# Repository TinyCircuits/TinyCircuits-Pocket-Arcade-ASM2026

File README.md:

# TinyCircuits Pocket Arcade
# ASM2026 Rev3

The design files are located under design_files/ for the TinyCircuits ASM2026 Rev 3 PCB. This is a tiny arcade game machine powered by Arduino software.

Format is in Cadsoft Eagle format - Eagle version 6.2 was used for the original design.

For more infomation on this, check out the product page at TinyCircuits.com: https://tinycircuits.com/collections/all/products/pocket-arcade

# License:

Design by TinyCircuits.
All design files are released under the Creative Commons Attribution Share-Alike 3.0 License, see the following link for details: http://creativecommons.org/licenses/by-sa/3.0

All text above must be included in any redistribution or derived design

This project uses designs and concepts developed as part of the Arduino project and the LilyPad project.  The TinyCircuits design files themselves (schematics, PCB and libraries) are not directly derived from these works' design files and have been created new, however the concepts and basic architecture behind the TinyDuino and TinyLily products are derived and we thank the hard work of the organizations below for their contributions to open-source hardware:
  
Original Arduino Uno Design by Team Arduino

LilyPad Arduino Design by Leah Buechley and Sparkfun Electronics

Please support the open-source hardware community

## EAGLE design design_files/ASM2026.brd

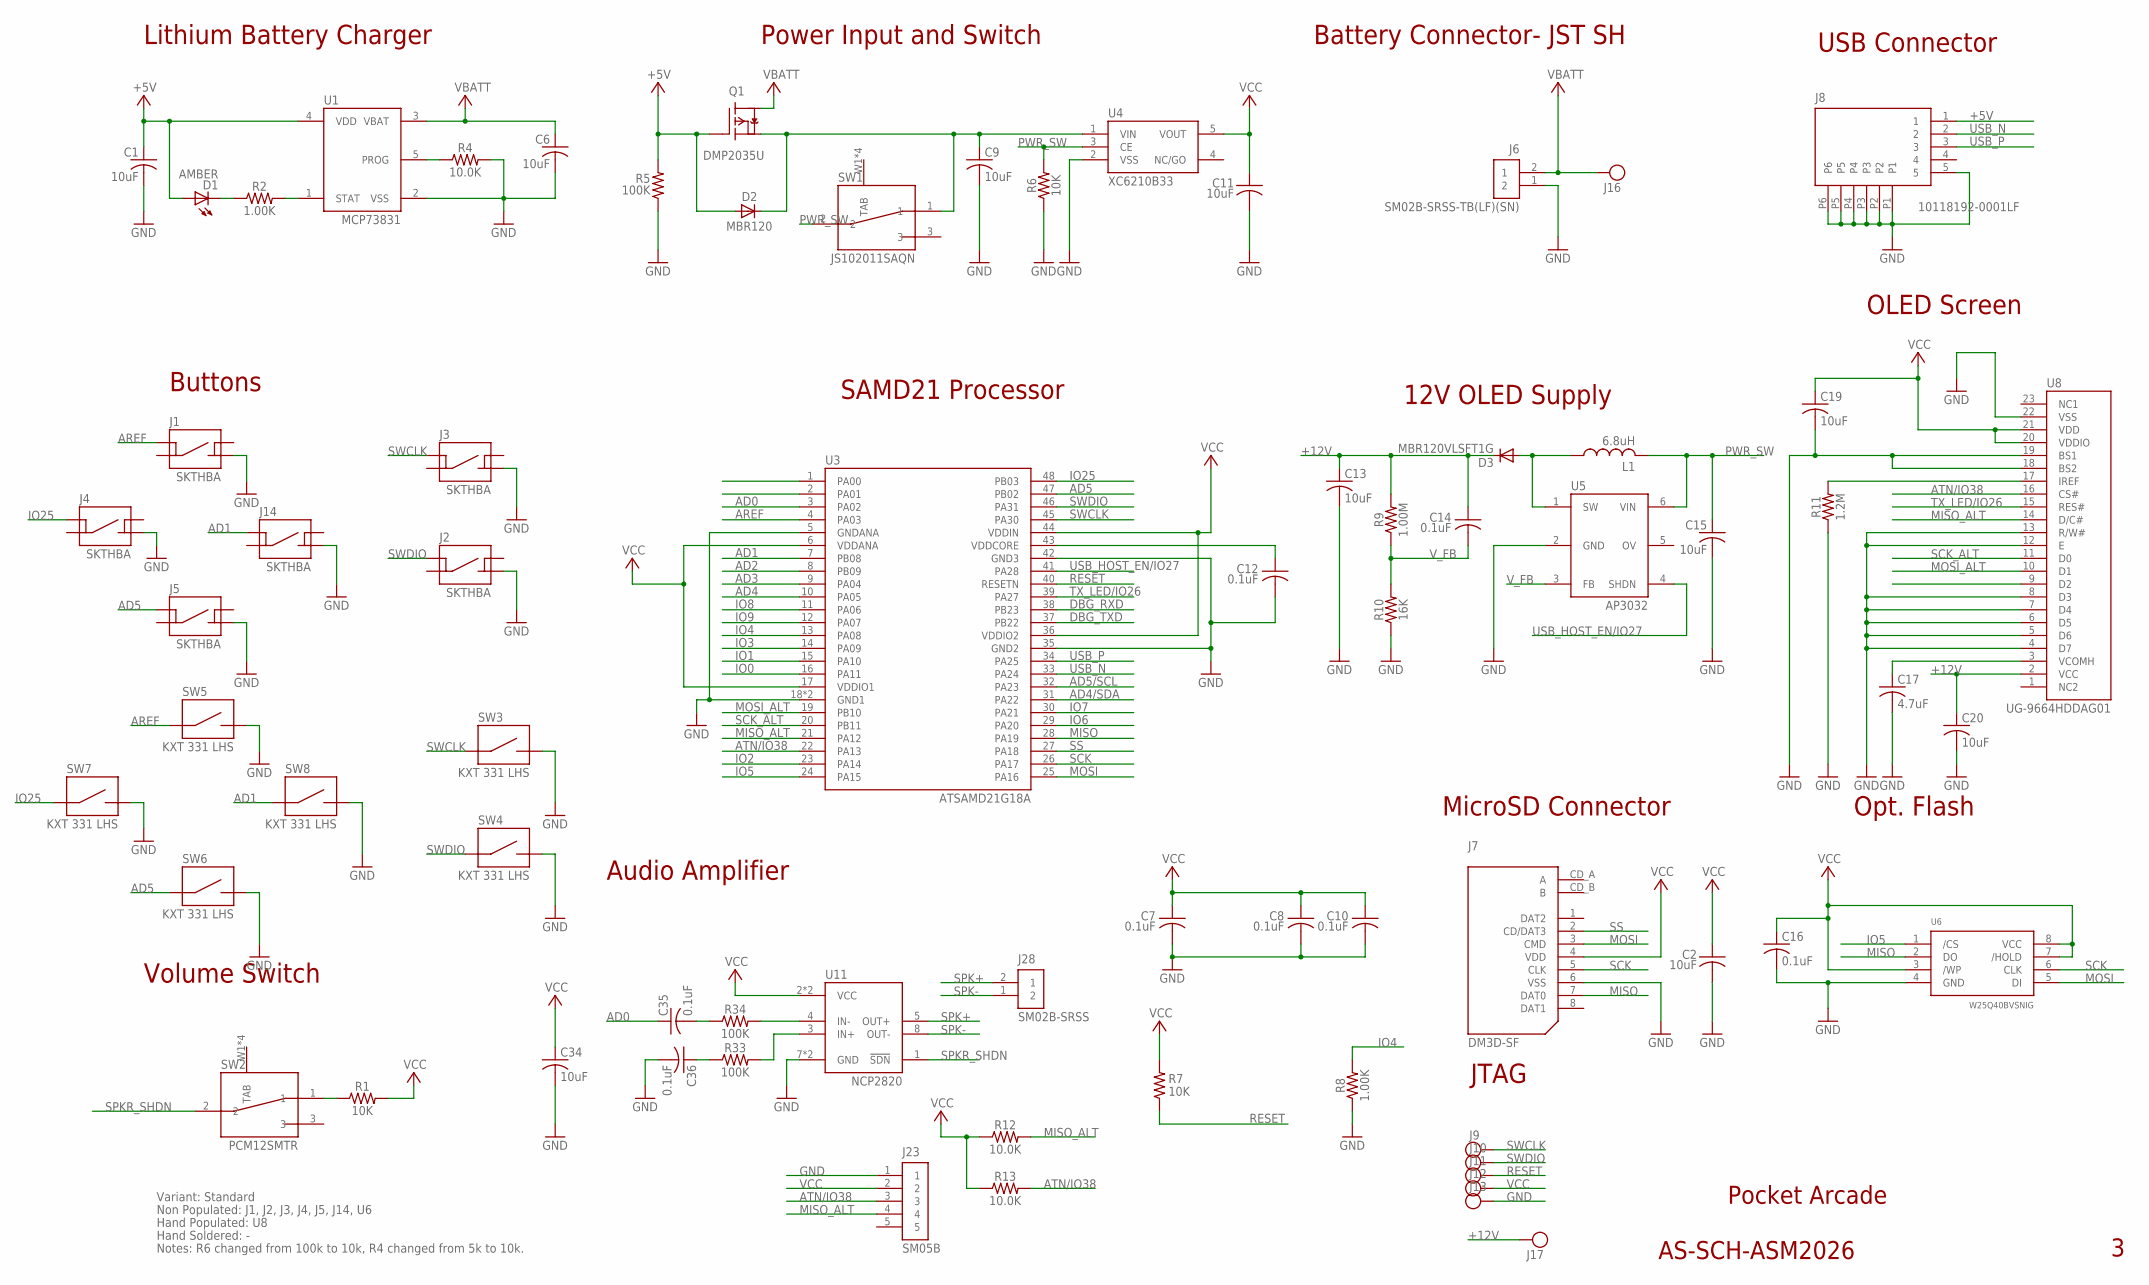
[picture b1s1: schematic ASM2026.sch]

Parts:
C1, C2, C6, C9, C11, C15, C34: 10uF; C0603; PARTNO AS-ITM-00002
C7, C8, C10, C12, C14: 0.1uF; C0402; PARTNO AS-ITM-00008
C13: 10uF; C0805; PARTNO AS-ITM-00045
C16, C35, C36: 0.1uF; C0402
C17: 4.7uF; 1206_CAP_TANT; PARTNO AS-ITM-00232
C19: 10uF; C0603
C20: 10uF; C0805
D1: AMBER; LNJ_LED; PARTNO AS-ITM-00026
D2: MBR120; SOD-123FL
D3: MBR120VLSFT1G; SOD-123FL
J1, J4, J5, J14: SKTHBA; SKTHBA_TACT; PARTNO AS-ITM-00369
J2, J3: SKTHBA; SKTHBA_TACT
J6: SM02B-SRSS-TB(LF)(SN); JST_SH_2X1
J7: DM3D-SF; SD_CARD
J8: 10118192-0001LF; MICRO_USB_ALT
J9, J10, J11, J12, J13, J16, J17: TEST_POINT; TEST_POINT_1MM
J23: SM05B; JST_SH_5X1
J28: SM02B-SRSS; JST_SH_2X1
L1: 6.8uH; R0805; PARTNO AS-ITM-00320
Q1: DMP2035U; SOT23A
R1, R6, R7: 10K; 0402; PARTNO AS-ITM-00032
R2, R8: 1.00K; 0402; PARTNO AS-ITM-00003
R4: 10.0K; 0402; PARTNO AS-ITM-00032
R5: 100K; 0402; PARTNO AS-ITM-00004
R9: 1.00M; 0402; PARTNO AS-ITM-00005
R10: 16K; 0402; PARTNO AS-ITM-00314
R11: 1.2M; 0402; PARTNO AS-ITM-00280
R12, R13: 10.0K; 0402
R33, R34: 100K; 0402
SW1: JS102011SAQN; PCM12SMTR; PARTNO AS-ITM-00220
SW2: PCM12SMTR
SW3, SW4, SW5, SW6, SW7, SW8: KXT 331 LHS; KXT_LHS_1
U1: MCP73831; SOT-23
U3: ATSAMD21G18A; QFN48; PARTNO AS-ITM-00273
U4: XC6210B33; SOT-25
U5: AP3032; SOT-23-6; PARTNO AS-ITM-00310
U6: W25Q40BVSNIG; 8-SOIC-N
U8: UG-9664HDDAG01; OLED_DISPLAY; PARTNO AS-ITM-00158
U11: NCP2820; WSON-8

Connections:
+5V: C1.1, D1.A, D2.A, J8.1, Q1.B (G), R5.2, U1.4 (VDD)
+12V: C13.1, C14.1, C20.1, D3.C, J17.P$1, R9.2, U8.2 (VCC)
AD0: C35.1, U3.3 (PA02)
AD1: J14.1, SW8.1, U3.7 (PB08)
AD2: U3.8 (PB09)
AD3: U3.9 (PA04)
AD4: U3.10 (PA05)
AD4/SDA: U3.31 (PA22)
AD5: J5.1, SW6.1, U3.47 (PB02)
AD5/SCL: U3.32 (PA23)
AREF: J1.1, SW5.1, U3.4 (PA03)
ATN/IO38: J23.3, R13.2, U3.22 (PA13), U8.16 (CS#)
DBG_RXD: U3.38 (PB23)
DBG_TXD: U3.37 (PB22)
GND: C1.2, C2.2, C6.2, C7.2, C8.2, C9.2, C10.2, C11.2, C12.2, C13.2, C15.2, C16.2, C17.2, C19.2, C20.2, C34.2, C36.2, J1.4, J2.4, J3.4, J4.4, J5.4, J6.1 (2), J7.6 (VSS), J8.5, J8.P1, J8.P2, J8.P3, J8.P4, J8.P5, J8.P6, J13.P$1, J14.4, J23.1, R4.2, R5.1, R6.1, R8.1, R10.1, R11.1, SW3.2, SW4.2, SW5.2, SW6.2, SW7.2, SW8.2, U1.2 (VSS), U3.5 (GNDANA), U3.18 (GND1), U3.35 (GND2), U3.42 (GND3), U3.EXP (GND1), U4.2 (VSS), U5.2 (GND), U6.4 (GND), U8.4 (D7), U8.5 (D6), U8.6 (D5), U8.7 (D4), U8.8 (D3), U8.12 (E), U8.13 (R/W#), U8.18 (BS2), U8.19 (BS1), U8.22 (VSS), U11.7 (GND), U11.9 (GND)
IO0: U3.16 (PA11)
IO1: U3.15 (PA10)
IO2: U3.23 (PA14)
IO3: U3.14 (PA09)
IO4: R8.2, U3.13 (PA08)
IO5: U3.24 (PA15), U6.1 (/CS)
IO6: U3.29 (PA20)
IO7: U3.30 (PA21)
IO8: U3.11 (PA06)
IO9: U3.12 (PA07)
IO25: J4.1, SW7.1, U3.48 (PB03)
MISO: J7.7 (DAT0), U3.28 (PA19), U6.2 (DO)
MISO_ALT: J23.4, R12.2, U3.21 (PA12), U8.14 (D/C#)
MOSI: J7.3 (CMD), U3.25 (PA16), U6.5 (DI)
MOSI_ALT: U3.19 (PB10), U8.10 (D1)
unnamed: R1.1, SW2.1
unnamed: D1.C, R2.1
unnamed: R4.1, U1.5 (PROG)
unnamed: R2.2, U1.1 (STAT)
unnamed: C12.1, U3.43 (VDDCORE)
unnamed: R11.2, U8.17 (IREF)
unnamed: C17.1, U8.3 (VCOMH)
unnamed: D3.A, L1.1, U5.1 (SW)
unnamed: R33.2, U11.3 (IN+)
unnamed: R34.2, U11.4 (IN-)
unnamed: C35.2, R34.1
unnamed: C36.1, R33.1
PWR_SW: C15.1, L1.2, R6.2, SW1.2, U4.3 (CE), U5.6 (VIN)
PWR_SWITCH: C9.1, D2.C, Q1.E (S), SW1.1, U4.1 (VIN)
RESET: J11.P$1, R7.1, U3.40 (RESETN)
SCK: J7.5 (CLK), U3.26 (PA17), U6.6 (CLK)
SCK_ALT: U3.20 (PB11), U8.11 (D0)
SPK+: J28.2 (1), U11.5 (OUT+)
SPK-: J28.1 (2), U11.8 (OUT-)
SPKR_SHDN: SW2.2, U11.1 (!SDN)
SS: J7.2 (CD/DAT3), U3.27 (PA18)
SWCLK: J3.1, J9.P$1, SW3.1, U3.45 (PA30)
SWDIO: J2.1, J10.P$1, SW4.1, U3.46 (PA31)
TX_LED/IO26: U3.39 (PA27), U8.15 (RES#)
USB_HOST_EN/IO27: U3.41 (PA28), U5.4 (SHDN)
USB_N: J8.2, U3.33 (PA24)
USB_P: J8.3, U3.34 (PA25)
VBATT: C6.1, J6.2 (1), J16.P$1, Q1.C (D), U1.3 (VBAT)
VCC: C2.1, C7.1, C8.1, C10.1, C11.1, C16.1, C19.1, C34.1, J7.4 (VDD), J12.P$1, J23.2, R1.2, R7.2, R12.1, R13.1, U3.6 (VDDANA), U3.17 (VDDIO1), U3.36 (VDDIO2), U3.44 (VDDIN), U4.5 (VOUT), U6.3 (/WP), U6.7 (/HOLD), U6.8 (VCC), U8.20 (VDDIO), U8.21 (VDD), U11.2 (VCC), U11.6 (VCC)
V_FB: C14.2, R9.1, R10.2, U5.3 (FB)

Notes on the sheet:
SAMD21 Processor
Power Input and Switch
Pocket Arcade
AS-SCH-ASM2026
Lithium Battery Charger
Battery Connector- JST SH
USB Connector
JTAG
12V OLED Supply
Buttons
Audio Amplifier
MicroSD Connector
Volume Switch
Opt. Flash
Non Populated: J1, J2, J3, J4, J5, J14, U6
Hand Populated: U8
Hand Soldered: -
Variant: Standard
Notes: R6 changed from 100k to 10k, R4 changed from 5k to 10k.
OLED Screen

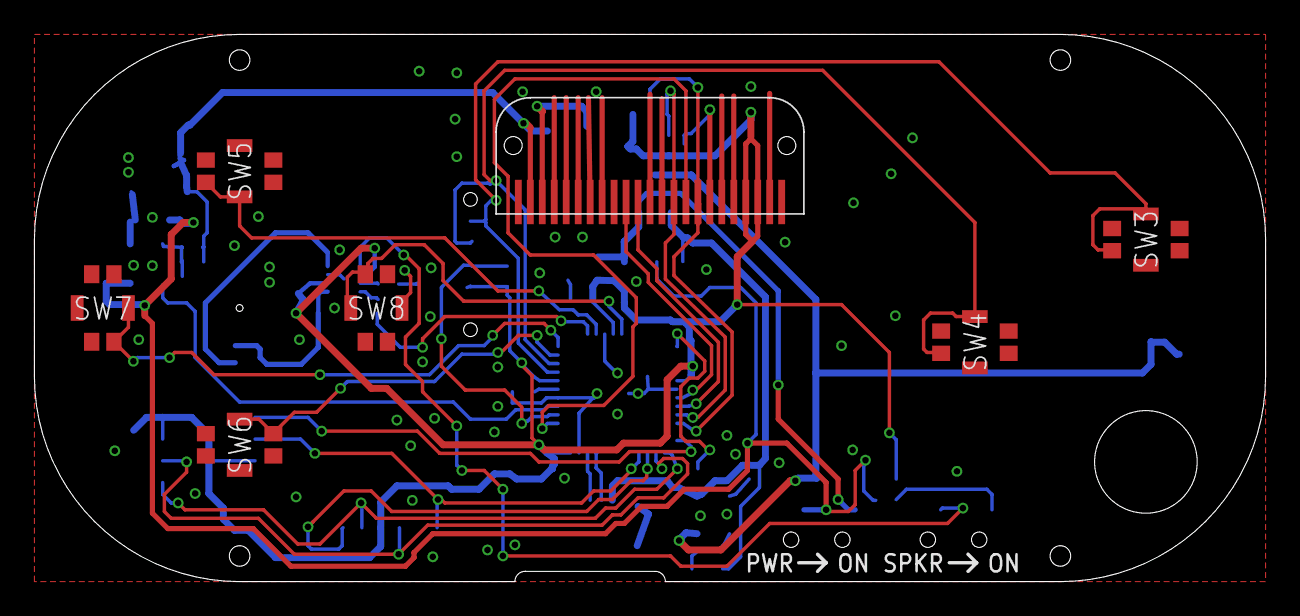
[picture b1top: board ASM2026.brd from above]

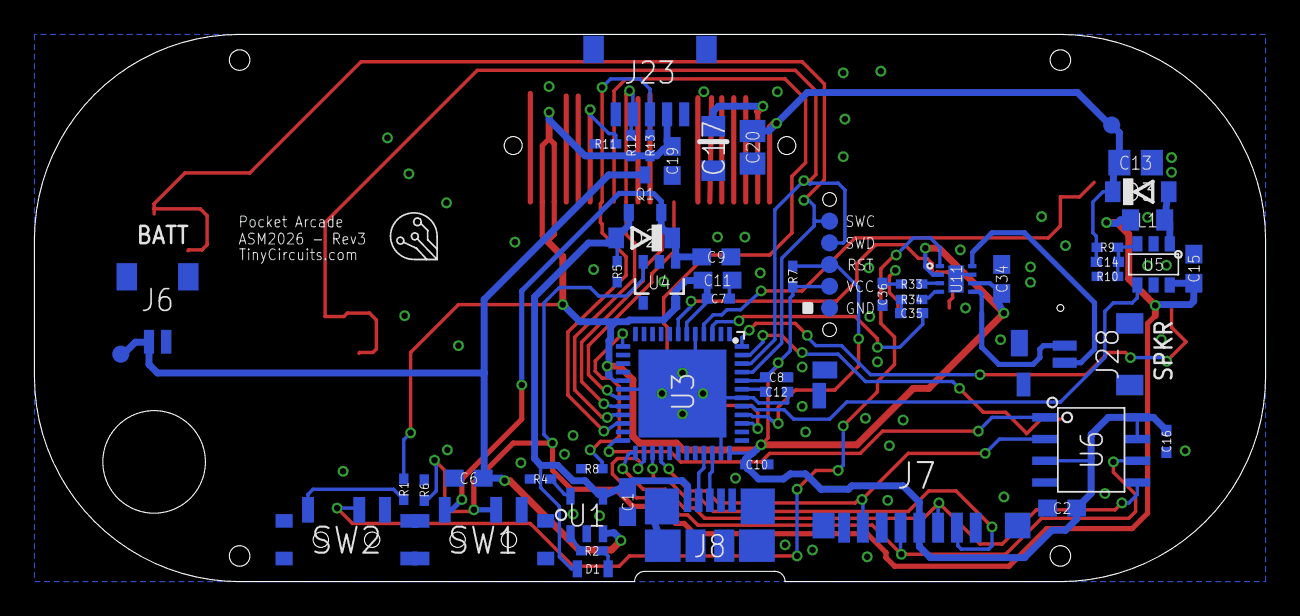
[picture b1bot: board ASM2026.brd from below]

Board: 2 copper layers, 72.0 x 32.0 mm, 72 parts (58 on the bottom side), 45 nets.

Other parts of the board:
U$1: DOCFIELD-TINYCIRCUITS-PCB

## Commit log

2019-08-19 Pocket Arcade git files
